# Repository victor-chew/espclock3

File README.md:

# ESPCLOCK3
Internet-enabled Analog Clock using ESP8266 and ATtiny85

### Description
This is version 3 of my [ESPClock](https://www.randseq.org/2016/10/hacking-analog-clock-to-sync-with-ntp.html) project.

The clock gets accurate time information from the Internet and makes sure the physical clock time is up-to-date. It also automatically detects your current timezone via browser geolocation and deals with daylight saving adjustments with no user intervention.

V1 uses the ESP-12E development board to drive a cheap $2 Ikea analog clock.

V2 uses the WeMOS D1 Mini and ATtiny85 to reduce power draw. That design yields a runtime of ~1 month.

V3 uses the ESP-07, ATtiny85 and PCF8563 RTC to reduce the power draw even further. This design yields at least 4 months of runtime on a set of readily-available 4 x 1.2V AA NiMH rechargables.

### Links:
* [Design](https://www.randseq.org/2020/05/espclock3-final-version.html)

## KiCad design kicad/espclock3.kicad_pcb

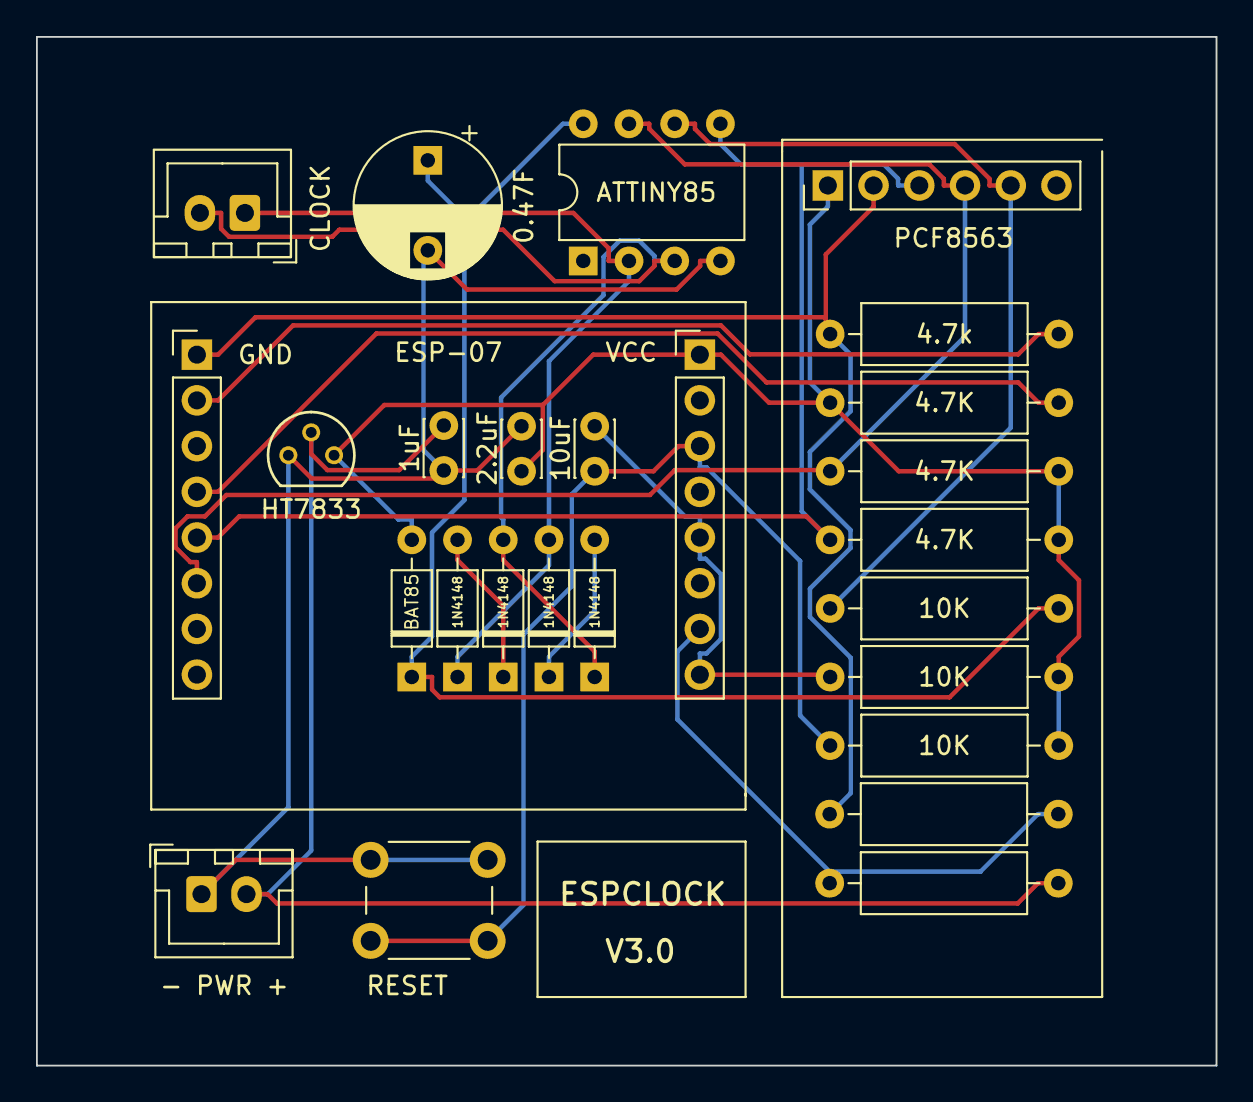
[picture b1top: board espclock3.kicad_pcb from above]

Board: 2 copper layers, 65.5 x 57.2 mm, 26 parts (0 on the bottom side), 17 nets.

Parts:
C1: 1uF; C_Disc_D3.0mm_W2.0mm_P2.50mm
C2: 2.2uF; C_Disc_D3.0mm_W2.0mm_P2.50mm
C3: 10uF; C_Disc_D3.0mm_W2.0mm_P2.50mm
C4: 0.47F; CP_Radial_D8.0mm_P5.00mm
D1: BAT85; D_DO-35_SOD27_P7.62mm_Horizontal
D2, D3, D4, D5: 1N4148; D_DO-35_SOD27_P7.62mm_Horizontal
ESP07-GND1, ESP07-VCC1: Conn_01x08_Female; PinHeader_1x08_P2.54mm_Vertical
J1: Quartz Clock; JST_XH_B2B-XH-A_1x02_P2.50mm_Vertical
J2: Battery; JST_XH_B2B-XH-A_1x02_P2.50mm_Vertical
J5: PCF8563; PinHeader_1x06_P2.54mm_Vertical
L1: HT7833; ht7333-a
R1, R4, R7, R9: 10K; R_Axial_DIN0309_L9.0mm_D3.2mm_P12.70mm_Horizontal
R2: 4.7k; R_Axial_DIN0309_L9.0mm_D3.2mm_P12.70mm_Horizontal
R3, R5, R6: 4.7K; R_Axial_DIN0309_L9.0mm_D3.2mm_P12.70mm_Horizontal
R8: 47K; R_Axial_DIN0309_L9.0mm_D3.2mm_P12.70mm_Horizontal
SW1: SW_Push; SW_PUSH_6mm
U3: ATtiny85-20PU; DIP-8_W7.62mm

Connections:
/ADC: ESP07-VCC1.7, R8.1, R9.2
/COT: J5.5, R7.1, U3.6
/GND: ESP07-GND1.1, J5.2, R2.1, R9.1
/GPIO0: ESP07-GND1.4, R3.2
/GPIO12: C3.1, ESP07-VCC1.3, R4.1, SW1.2
/GPIO15: ESP07-GND1.2, R2.2
/GPIO16: C3.2, ESP07-VCC1.5, ESP07-VCC1.8, R1.1
/SCL: ESP07-GND1.6, J5.4, R5.1, U3.7
/SDA: ESP07-GND1.5, J5.3, R6.1, U3.5
/VCC: C2.1, D1.2, ESP07-VCC1.1, J5.1, L1.3, R1.2, R3.1, R4.2, R5.2, R6.2
unnamed: C1.1, J2.2, L1.2, R8.2
unnamed: C1.2, C2.2, C4.2, J2.1, L1.1, SW1.1, U3.4
unnamed: C4.1, D1.1, R7.2, U3.8
unnamed: D2.1, D3.2, J1.1, U3.2
unnamed: D2.2, D4.1
unnamed: D3.1, D5.2
unnamed: D4.2, D5.1, J1.2, U3.3

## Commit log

2020-05-24 Updated README.md
    Updated README.md
2020-05-24 Fixed typo in README.md
    Fixed typo in README.md
2021-03-14 Updated to v3.1
    Updated to v3.1
2021-03-17 Added .gitignore for kicad folder
2021-12-19 Change dump
